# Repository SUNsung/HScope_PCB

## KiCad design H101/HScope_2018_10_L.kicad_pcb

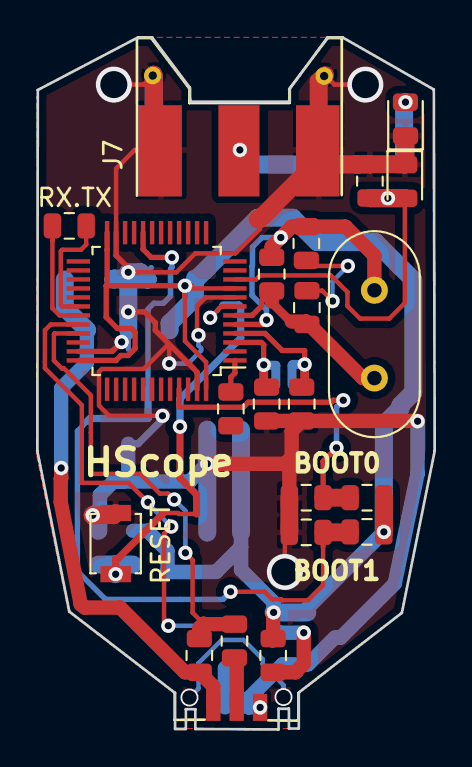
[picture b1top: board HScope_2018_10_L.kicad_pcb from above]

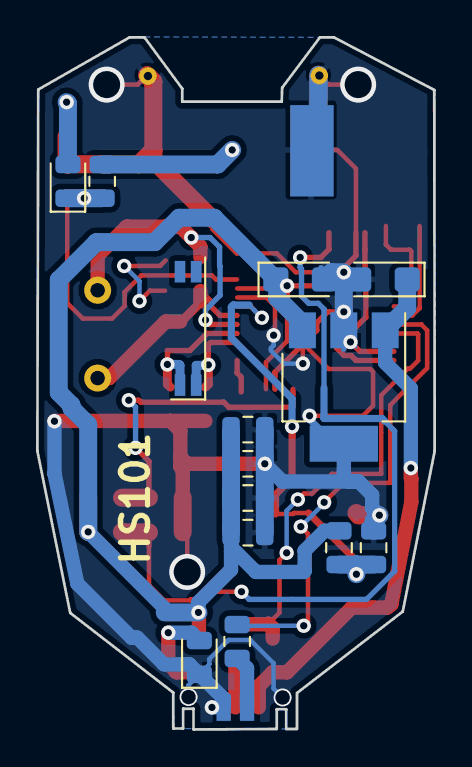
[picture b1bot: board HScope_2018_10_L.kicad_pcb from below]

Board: 2 copper layers, 22.1 x 38.5 mm, 36 parts (14 on the bottom side), 22 nets.

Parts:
C1, C3: 0.33uF; CP_EIA-3216-18_Kemet-A
C2: 1000 nF; C_0805_2012Metric
C4, C5, C6, C7: 100nF; C_0805_2012Metric
C8, C9, C10, C11: 20pF; C_0805_2012Metric
D1: 0805; D_0805_2012Metric
D2, D3, D4: DIODE; D_0805_2012Metric
J1: USB_B_Micro; mikroUSB_SMD
J2, J3, J4, J5: Джампер; R_0805_2012Metric
J7: BNS; SMA_Molex_73251-1153_EdgeMount_Horizontal
R1, R8: 10k; R_0805_2012Metric
R2, R4: 20R; R_0805_2012Metric
R3: 4,7k; R_0805_2012Metric
R5: 1M; R_0805_2012Metric
R6: 1k; R_0805_2012Metric
R7: 0R; R_0805_2012Metric
R9: 2k; R_0805_2012Metric
RX.TX: RX\TX; R_0805_2012Metric
SW1: RESET; SW_SPST_B3U-1000P
U1: MC33275ST-3.3T3G; SOT-223
U2: STM32F103C8Tx; LQFP-48_7x7mm_P0.5mm
Y1: 32.678kHz; Crystal_SMD_SeikoEpson_MC146-4Pin_6.7x1.5mm
Y2: 8MHz; Crystal_HC49-4H_Vertical

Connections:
A0: D2.1, D3.2, R8.2, R9.2, U2.10
BOOT0: J2.1, J4.2, U2.45
BOOT1: J3.1, J5.2, U2.20
D+: R2.1, R3.1, U2.33
D-: R4.2, U2.32
GNDREF: C1.2, C2.2, C3.2, C4.2, C5.2, C6.2, C7.2, C8.1, C10.2, D1.1, D3.1, D4.1, J1.4, J1.5, J4.1, J5.1, J7.2, R9.1, SW1.2, U1.2, U2.8, U2.23, U2.35, U2.47
IN_U: J7.1, R8.1
unnamed: C9.1, C11.2
unnamed: D1.2, R6.2
unnamed: D2.2, D4.2
unnamed: J1.2, R4.1
unnamed: J1.3, R2.2
OC_1_IN: C8.2, U2.3, Y1.1
OC_1_OUT: C10.1, U2.4, Y1.4
OC_2_IN: C9.2, R5.2, U2.5, Y2.1
OC_2_OUT: C11.1, R5.1, U2.6, Y2.2
RESET: C2.1, R1.1, SW1.1, U2.7
RX: RX.TX.2, U2.31
TX: RX.TX.1, U2.30
VCC: C3.1, C4.1, C5.1, C6.1, C7.1, J2.2, J3.2, R1.2, R6.1, U1.3, U2.9, U2.24, U2.36, U2.48
V_BAT: R7.1, U2.1
V_IN: C1.1, J1.1, R3.2, U1.1

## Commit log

2018-10-24 Create LICENSE
2019-01-08 Rename HScope_2018_10_L.kicad_pcb to H101/HScope_2018_10_L.kicad_pcb
2019-01-08 Rename HScope_2018_10_L.sch to H101/HScope_2018_10_L.sch
